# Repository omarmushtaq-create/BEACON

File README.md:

# BEACON
All the code, cad, and PCB design for my low cost air quailty monitoring station.

## Prerequisites

1. You need to create an InfluxDB account and Database. Here is a guide that will help you do this https://docs.influxdata.com/influxdb/v2/get-started/setup/

## How to use

1. First use the provided STEP file to create a 3d model of the case
2. Use whatever fabrication method you would prefer (3d printing, CNC, Woodworking, Pottery, Blacksmithing etc) to create the case. Just make sure that it is water tight.
3. Use the provided Gerbers.zip in /PCB/Gerbers.zip to manufacture your PCB with your PCB manufacturer of choice (I recommend either JLBPCB or PCBway)
4. Buy and solder the components or use PCBA serveries to have your manufacturer assemble them for you
5. Install the Solar Panel Power Manager (SPPM), the ZPH02 sensor and the solar panel in the correct positions. For the solar panel you will need to solder jumpers from the + and - out terminals to the + and - in terminals of the SPPM. Connect the the 5v and GND out of the SPPM to the 2 pin connector on the board. Then connect the ZHP02 pinouts to the 5pin input on the PCB. (You can see a basic flow in /Assets/Wire_Diagarm.drawio.png). To make sure you have connected all the pins to the correct place you can reference the schematic at /PCB/BEACON.kicad_pcb
6. Update the config.h file in /Firmware/include/config.h and add you wifi SSID, Password and add a new device name (The device name you should not enter at this point are *esp32_node_01*). This allows the data to be sent to the central server and displayed on the website. 
7. Upload the modified code provided to the PCB.
8. Install the finished PCB into the case along with the solar panel and ZPH dust sensor and lithium ion batteries.
9. Install it to a pole or fixture using zip ties.
10. And your done! Now you can view and access your data from the website.

## Adding to BEACON
If you want to help contribute to the BEACON site at https://beaconoffical.netlify.app/, email me at beacon.offical2026@gmail.com

### If you have any ideas to improve the Code, Cad or PCB design email me!

Made with ❤️ By Omar

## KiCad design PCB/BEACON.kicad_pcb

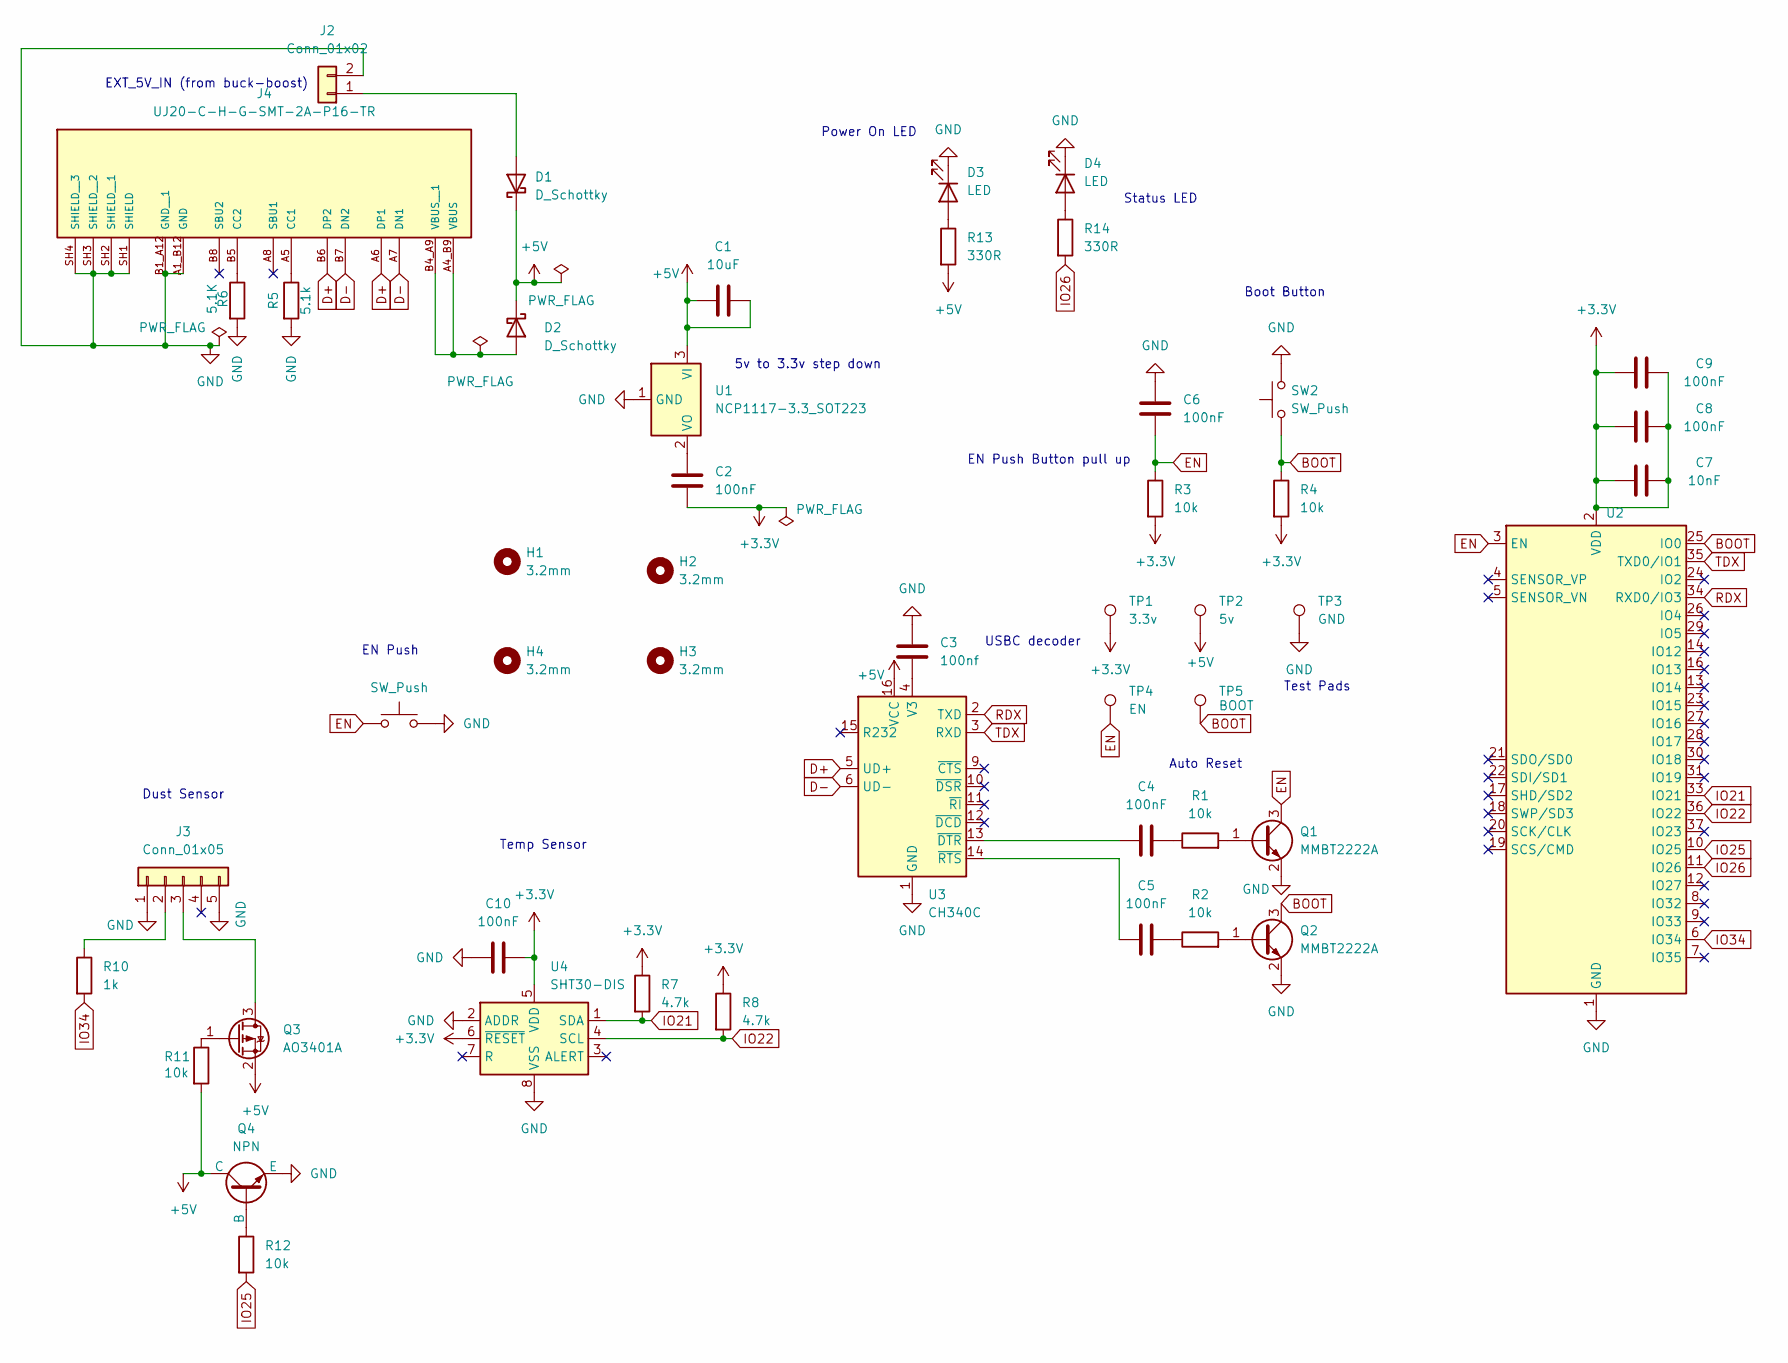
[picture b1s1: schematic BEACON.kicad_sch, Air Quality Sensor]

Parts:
C1: 10uF; C_0805_2012Metric
C2, C4, C5, C6, C8, C9, C10: 100nF; C_0805_2012Metric
C3: 100nf; C_0805_2012Metric
C7: 10nF; C_0805_2012Metric
D1, D2: D_Schottky; D_DO-41_SOD81_P10.16mm_Horizontal
D3, D4: LED; LED_D5.0mm
H1, H2, H3, H4: 3.2mm; MountingHole_3.2mm_M3
J2: Conn_01x02; PinHeader_1x02_P2.54mm_Vertical
J3: Conn_01x05; PinHeader_1x05_P2.54mm_Vertical
J4: UJ20-C-H-G-SMT-2A-P16-TR; SAMESKY_UJ20-C-H-G-SMT-2A-P16-TR; PARTREV 1.0
Q1, Q2: MMBT2222A; SOT-23
Q3: AO3401A; SOT-23
Q4: NPN; SOT-23
R1, R2, R3, R4, R11, R12: 10k; R_0805_2012Metric
R5: 5.1k; R_0805_2012Metric
R6: 5.1K; R_0805_2012Metric
R7, R8: 4.7k; R_0805_2012Metric
R10: 1k; R_0805_2012Metric
R13, R14: 330R; R_0805_2012Metric
SW1, SW2: SW_Push; SW_PUSH_6mm
TP1: 3.3v; TestPoint_Pad_D1.5mm
TP2: 5v; TestPoint_Pad_D1.5mm
TP3: GND; TestPoint_Pad_D1.5mm
TP4: EN; TestPoint_Pad_D1.5mm
TP5: BOOT; TestPoint_Pad_D1.5mm
U1: NCP1117-3.3_SOT223; SOT-223-3_TabPin2
U2: ESP32-WROOM-32
U3: CH340C; SOIC-16_3.9x9.9mm_P1.27mm
U4: SHT30-DIS; SHT3x-x-P

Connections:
+3.3V: C2.2, C7.1, C7.2, C8.1, C8.2, C9.1, C9.2, C10.2, R3.2, R4.2, R7.1, R8.1, TP1.1 (1_1), U2.2 (VDD), U4.5 (VDD), U4.6 (~RESET)
+5V: C1.1, C1.2, D1.1 (K), D2.1 (K), Q3.2 (S), Q4.1 (C), R11.2, R13.2, TP2.1 (1_1), U1.3 (VI), U3.16 (VCC)
BOOT: Q2.3 (C), R4.1, SW2.1, TP5.1 (1_1), U2.25 (IO0)
D+: J4.A6 (DP1), J4.B6 (DP2), U3.5 (UD+)
D-: J4.A7 (DN1), J4.B7 (DN2), U3.6 (UD-)
EN: C6.2, Q1.3 (C), R3.1, SW1.1, TP4.1 (1_1), U2.3 (EN)
GND: C3.1, C6.1, C10.1, D3.1 (K), D4.1 (K), J2.2, J3.1, J3.5, J4.A1_B12 (GND), J4.B1_A12 (GND__1), J4.SH1 (SHIELD), J4.SH2 (SHIELD__1), J4.SH3 (SHIELD__2), J4.SH4 (SHIELD__3), Q1.2 (E), Q2.2 (E), Q4.3 (E), R5.2, R6.2, SW1.2, SW2.2, TP3.1 (1_1), U1.1 (GND), U2.1 (GND), U2.15 (GND), U2.38 (GND), U2.39 (GND), U3.1 (GND), U4.2 (ADDR), U4.8 (VSS), U4.9 (VSS)
IO21: R7.2, U2.33 (IO21), U4.1 (SDA)
IO22: R8.2, U2.36 (IO22), U4.4 (SCL)
IO25: R12.2, U2.10 (IO25)
IO26: R14.2, U2.11 (IO26)
IO34: R10.2, U2.6 (IO34)
unnamed: C4.2, R1.1
unnamed: C5.2, R2.1
unnamed: D1.2 (A), J2.1
unnamed: D2.2 (A), J4.A4_B9 (VBUS), J4.B4_A9 (VBUS__1)
unnamed: D3.2 (A), R13.1
unnamed: D4.2 (A), R14.1
unnamed: J3.2, R10.1
unnamed: J3.3, Q3.3 (D)
unnamed: J4.A5 (CC1), R5.1
unnamed: J4.B5 (CC2), R6.1
unnamed: Q1.1 (B), R1.2
unnamed: Q2.1 (B), R2.2
unnamed: Q3.1 (G), R11.1
unnamed: Q4.2 (B), R12.1
unnamed: C2.1, U1.2 (VO)
unnamed: C3.2, U3.4 (V3)
unnamed: C4.1, U3.13 (~DTR)
unnamed: C5.1, U3.14 (~RTS)
RDX: U2.34 (RXD0/IO3), U3.2 (TXD)
TDX: U2.35 (TXD0/IO1), U3.3 (RXD)

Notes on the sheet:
EXT_5V_IN (from buck-boost)
Power On LED
Auto Reset
Status LED
EN Push Button pull up
EN Push
Temp Sensor
5v to 3.3v step down
USBC decoder
Dust Sensor
Boot Button
Test Pads

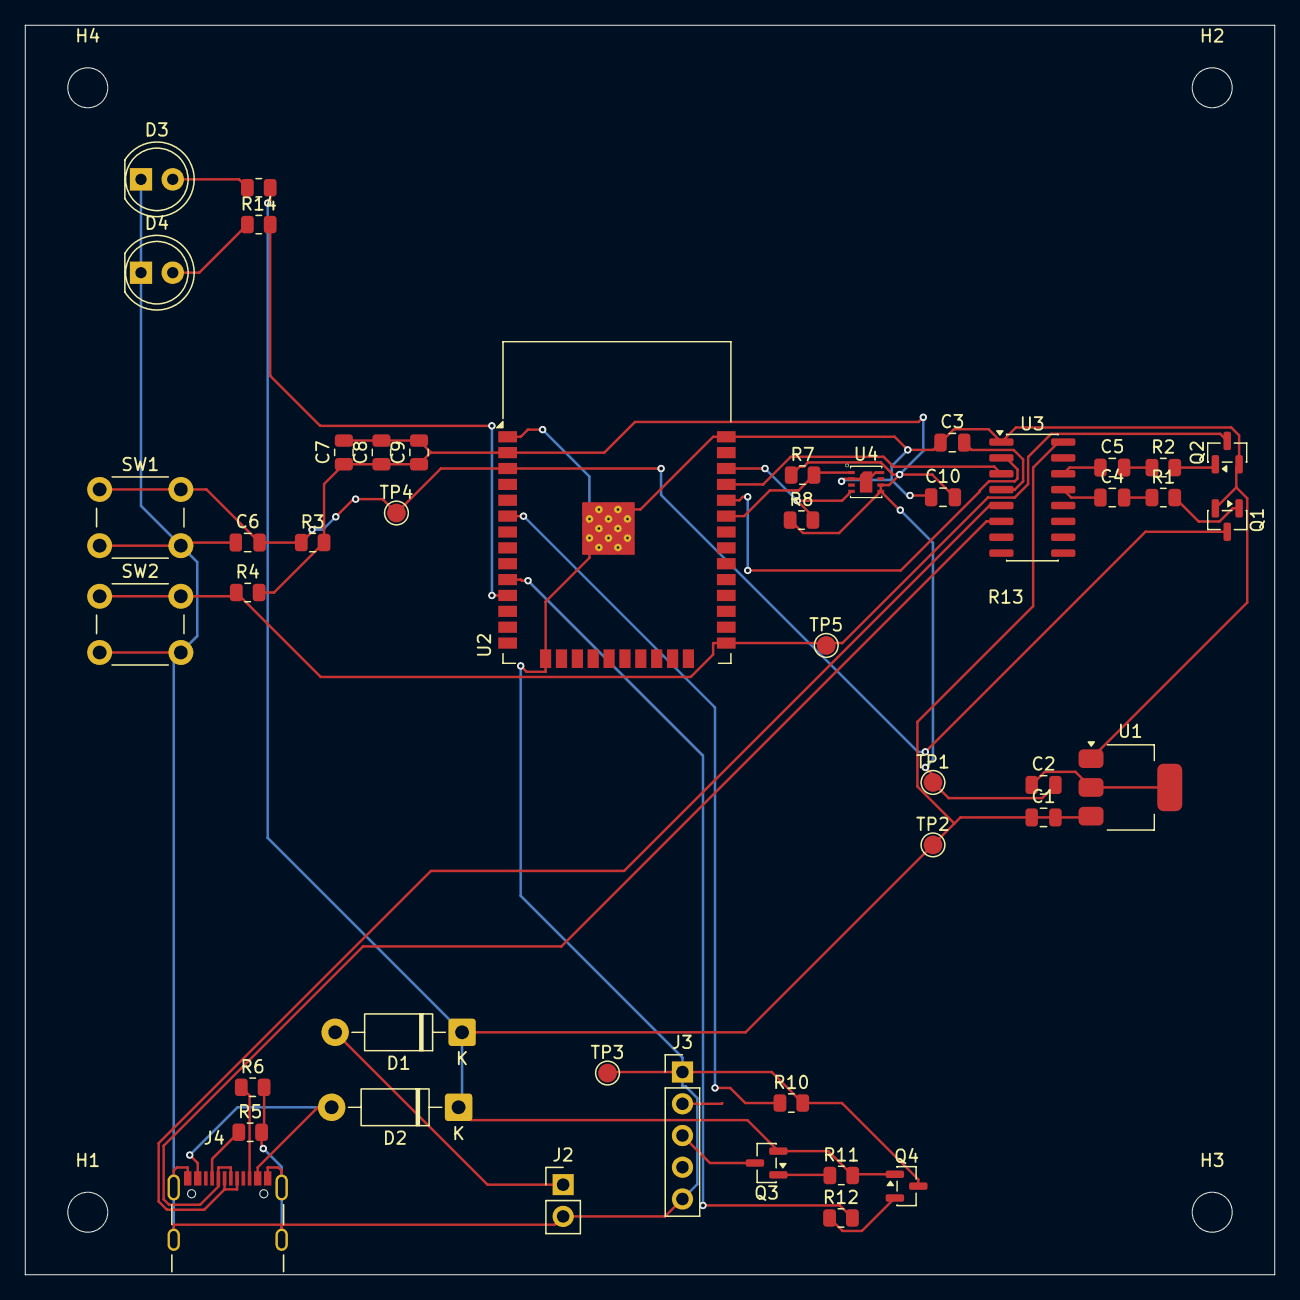
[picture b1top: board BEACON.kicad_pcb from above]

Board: 2 copper layers, 100.0 x 100.0 mm, 49 parts (0 on the bottom side), 32 nets.
